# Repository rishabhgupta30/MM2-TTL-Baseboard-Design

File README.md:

# MM2-TTL-Baseboard-Design
Baseboard Design for MM2 TTL Module using KiCAD

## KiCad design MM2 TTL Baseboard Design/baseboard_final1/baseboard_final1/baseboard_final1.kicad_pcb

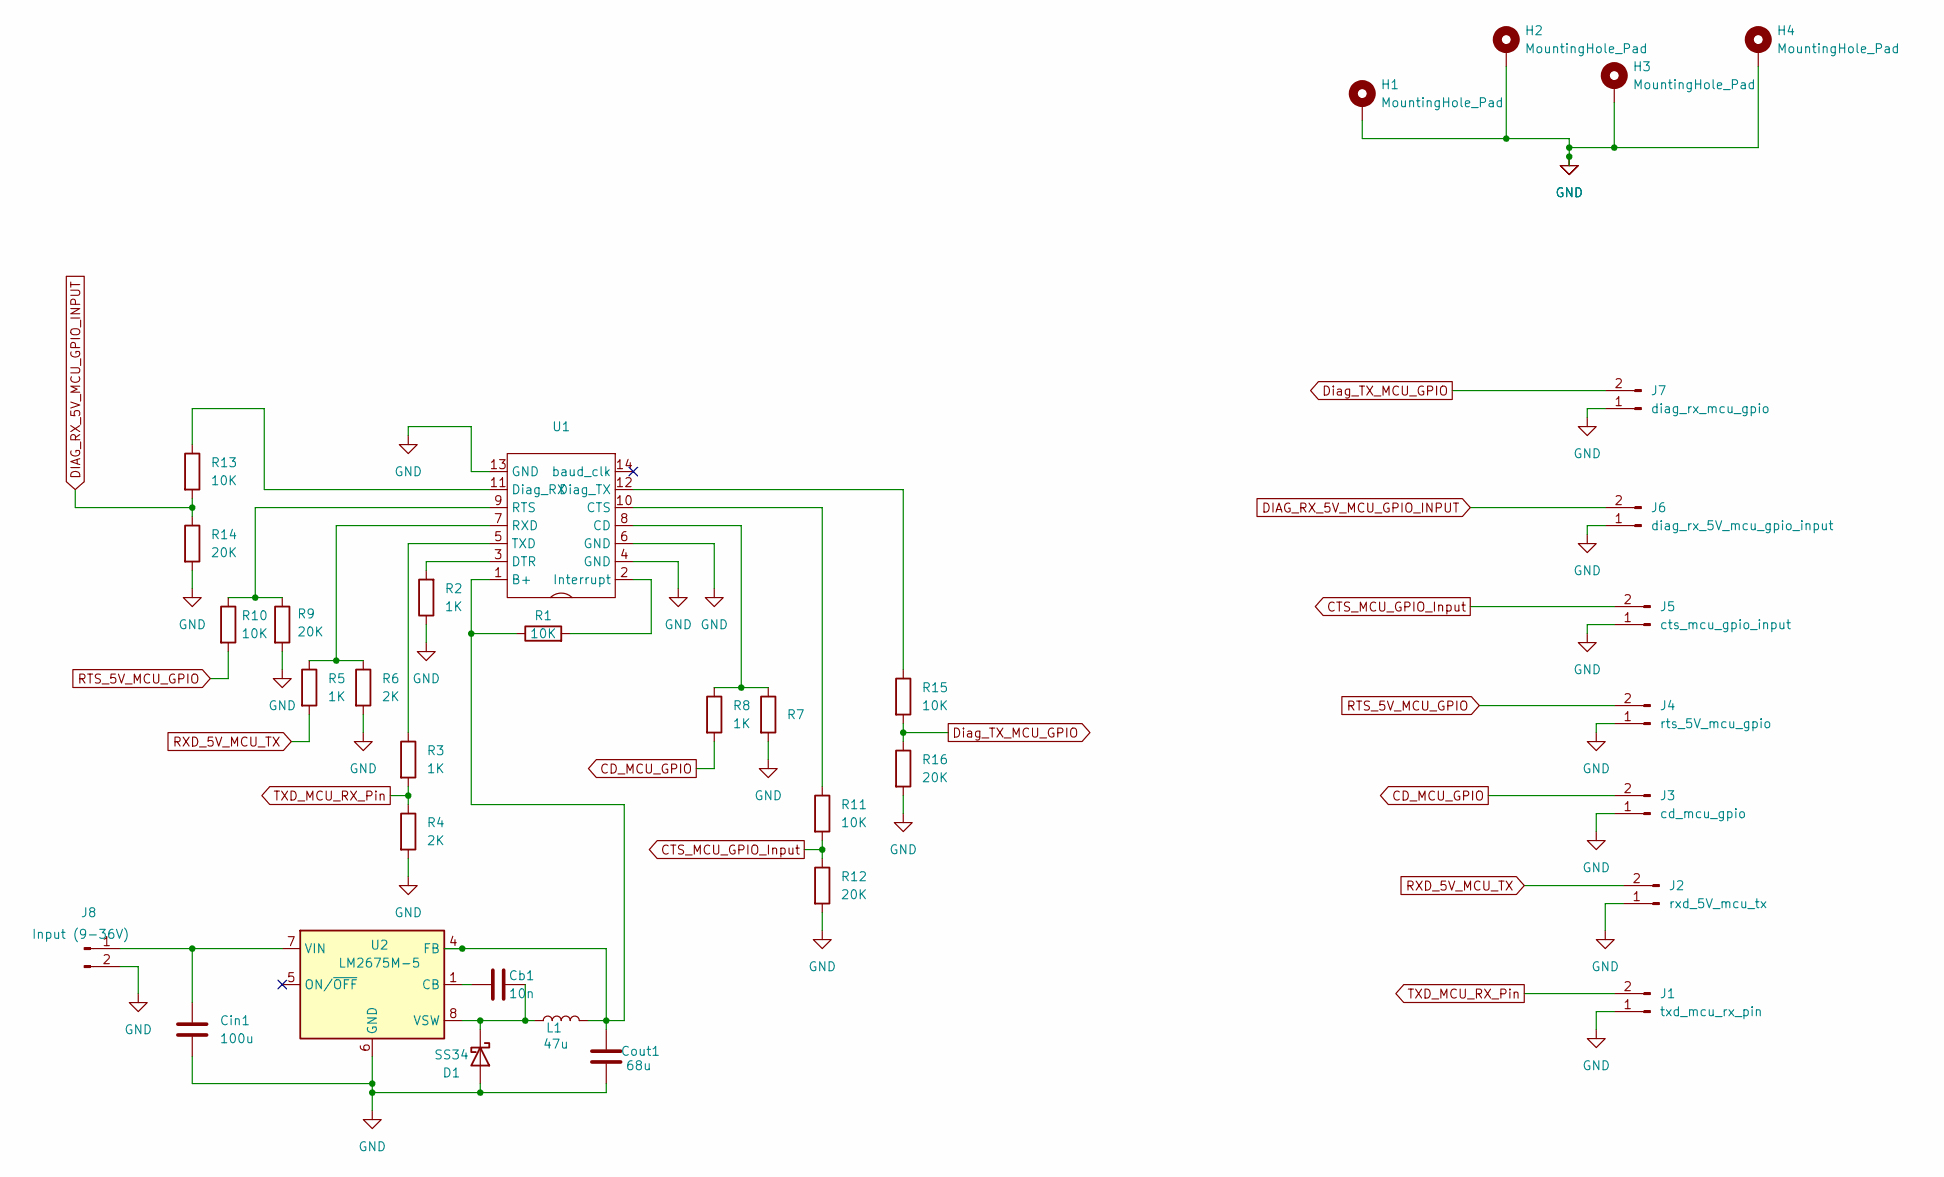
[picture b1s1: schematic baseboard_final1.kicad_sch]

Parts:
Cb1: 10n; C_0402_1005Metric
Cin1: 100u; C_0402_1005Metric
Cout1: 68u; C_1206_3216Metric
D1: SS34; D_SMA
H1, H2, H3, H4: MountingHole_Pad; MountingHole_2.2mm_M2_Pad_Via
J1: txd_mcu_rx_pin; PinHeader_1x02_P2.54mm_Vertical
J2: rxd_5V_mcu_tx; PinHeader_1x02_P2.54mm_Vertical
J3: cd_mcu_gpio; PinHeader_1x02_P2.54mm_Vertical
J4: rts_5V_mcu_gpio; PinHeader_1x02_P2.54mm_Vertical
J5: cts_mcu_gpio_input; PinHeader_1x02_P2.54mm_Vertical
J6: diag_rx_5V_mcu_gpio_input; PinHeader_1x02_P2.54mm_Vertical
J7: diag_rx_mcu_gpio; PinHeader_1x02_P2.54mm_Vertical
J8: Input (9-36V); PinHeader_1x02_P2.54mm_Vertical
L1: 47u; L_Bourns_SRR1260
R1, R10, R11, R13, R15: 10K; R_0603_1608Metric
R2, R3, R5, R8: 1K; R_0603_1608Metric
R4, R6, R7: 2K; R_0603_1608Metric
R9, R12, R14, R16: 20K; R_0603_1608Metric
U1: PinSocket_2x07_P2.54mm_Vertical
U2: LM2675M-5; SOIC-8_3.9x4.9mm_P1.27mm

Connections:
CD_MCU_GPIO: J3.2, R8.2
CTS_MCU_GPIO_Input: J5.2, R11.2, R12.1
DIAG_RX_5V_MCU_GPIO_INPUT: J6.2, R13.2, R14.1
Diag_TX_MCU_GPIO: J7.2, R15.2, R16.1
GND: Cin1.1, Cout1.1, D1.2 (A), H1.1, H2.1, H3.1, H4.1, J1.1, J2.1, J3.1, J4.1, J5.1, J6.1, J7.1, J8.2, R2.1, R4.2, R6.2, R7.2, R9.2, R12.2, R14.2, R16.2, U1.4 (GND), U1.6 (GND), U1.13 (GND), U2.6 (GND)
unnamed: Cb1.2, D1.1 (K), L1.1, U2.8 (VSW)
unnamed: Cin1.2, J8.1, U2.7 (VIN)
unnamed: Cout1.2, L1.2, R1.1, U1.1 (B+), U2.4 (FB)
unnamed: R7.1, R8.1, U1.8 (CD)
unnamed: R11.1, U1.10 (CTS)
unnamed: R2.2, U1.3 (DTR)
unnamed: R13.1, U1.11 (Diag_RX)
unnamed: R15.1, U1.12 (Diag_TX)
unnamed: R1.2, U1.2 (Interrupt)
unnamed: R9.1, R10.1, U1.9 (RTS)
unnamed: R5.1, R6.1, U1.7 (RXD)
unnamed: R3.1, U1.5 (TXD)
unnamed: Cb1.1, U2.1 (CB)
RTS_5V_MCU_GPIO: J4.2, R10.2
RXD_5V_MCU_TX: J2.2, R5.2
TXD_MCU_RX_Pin: J1.2, R3.2, R4.1

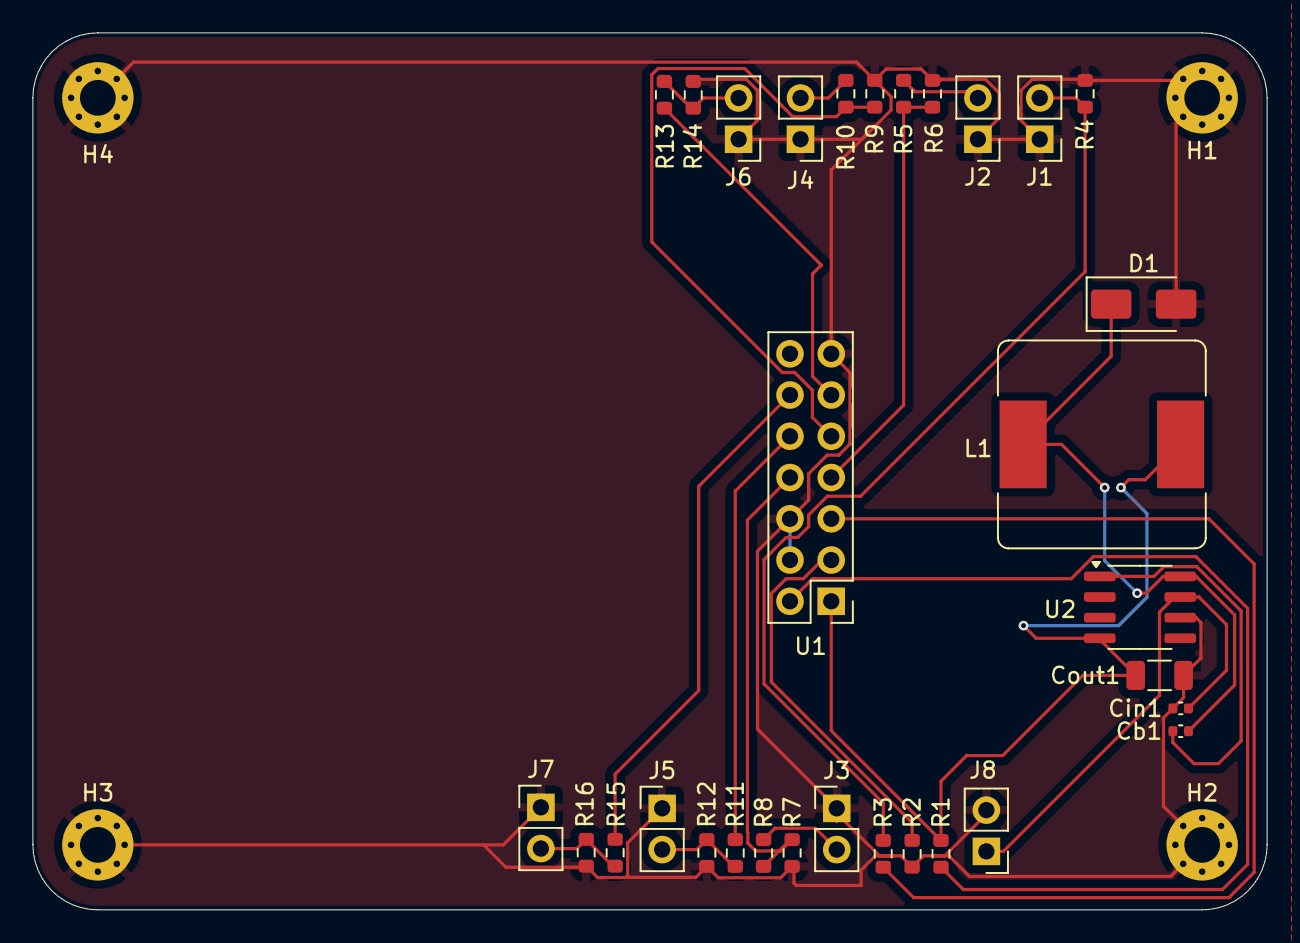
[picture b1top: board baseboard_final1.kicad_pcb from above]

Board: 2 copper layers, 76.0 x 54.0 mm, 35 parts (0 on the bottom side), 21 nets.

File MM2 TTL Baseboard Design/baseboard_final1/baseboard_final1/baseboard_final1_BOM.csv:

Reference,Value,Datasheet,Footprint,Qty,DNP
Cb1 hello,10n,~,Capacitor_SMD:C_0402_1005Metric,1,
Cin1,100u,~,Capacitor_SMD:C_0402_1005Metric,1,
Cout1,68u,~,Capacitor_SMD:C_1206_3216Metric,1,
D1,SS34,https://www.vishay.com/docs/88751/ss32.pdf,Diode_SMD:D_SMA,1,
J1,txd_mcu_rx_pin,~,Connector_PinHeader_2.54mm:PinHeader_1x02_P2.54mm_Vertical,1,
J2,rxd_5V_mcu_tx,~,Connector_PinHeader_2.54mm:PinHeader_1x02_P2.54mm_Vertical,1,
J3,cd_mcu_gpio,~,Connector_PinHeader_2.54mm:PinHeader_1x02_P2.54mm_Vertical,1,
J4,rts_5V_mcu_gpio,~,Connector_PinHeader_2.54mm:PinHeader_1x02_P2.54mm_Vertical,1,
J5,cts_mcu_gpio_input,~,Connector_PinHeader_2.54mm:PinHeader_1x02_P2.54mm_Vertical,1,
J6,diag_rx_5V_mcu_gpio_input,~,Connector_PinHeader_2.54mm:PinHeader_1x02_P2.54mm_Vertical,1,
J7,diag_rx_mcu_gpio,~,Connector_PinHeader_2.54mm:PinHeader_1x02_P2.54mm_Vertical,1,
J8,Input (9-36V),~,Connector_PinHeader_2.54mm:PinHeader_1x02_P2.54mm_Vertical,1,
L1,47u,~,Inductor_SMD:L_Bourns_SRR1260,1,
"R1,R10,R11,R13,R15",10K,~,Resistor_SMD:R_0603_1608Metric,5,
"R2,R3,R5,R8",1K,~,Resistor_SMD:R_0603_1608Metric,4,
"R4,R6,R7",2K,~,Resistor_SMD:R_0603_1608Metric,3,
"R9,R12,R14,R16",20K,~,Resistor_SMD:R_0603_1608Metric,4,
U1,~,,Connector_PinSocket_2.54mm:PinSocket_2x07_P2.54mm_Vertical,1,
U2,LM2675M-5,http://www.ti.com/lit/ds/symlink/lm2675.pdf,Package_SO:SOIC-8_3.9x4.9mm_P1.27mm,1,
